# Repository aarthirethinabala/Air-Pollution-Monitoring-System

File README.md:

# Air Pollution Monitoring System
An Arduino-based air pollution and vehicle exhaust monitoring system designed to detect multiple gases and environmental conditions using gas sensors and a temperature/humidity sensor.

## Project Status
PCB Design Completed

## Overview
This project is designed to monitor air pollution using using multiple gas sensors connected to an Arduino Uno.
The system uses gas sensors to detect different pollutants and provides visual and audible indications based on the detected conditions.
Temperature and humidity are also monitored, and the readings can be displayed using an OLED display.
The PCB was designed as a controller and interface board, with the sensor modules connected externally through the provided connections.

## Components
- Arduino Uno
- MQ-7 gas sensor
- MQ-2 gas sensor
- MQ-135 gas sensor
- DHT22 temperature and humidity sensor
- OLED display
- Green LED
- Yellow LED
- Red LED
- Buzzer
- Resistors and supporting components

## Tools Used
- KiCad
- Schematic Editor
- PCB Editor
- 3D Viewer

## Design Process
The PCB was developed through the following stages:
1. Schematic design
2. Electrical Rules Check (ERC)
3. Footprint assignment
4. Component placement
5. Board outline creation
6. PCB routing
7. Copper zone creation
8. Design Rules Check (DRC)

## PCB Design
The completed PCB contains the Arduino interface connections, sensor connections, display connection, indicator LEDs, buzzer, and supporting circuitory.
The external sensor modules are connected to the PCB through their respective headers.

## Project Images
### Schematic

### PCB Layout

### 3D View

## What I Learned
- PCB schematic design
- ERC checking
- Footprint selection and assignment
- PCB component placement
- PCB routing
- Copper zones
- DRC checking
- Designing interfaces for external sensor modules

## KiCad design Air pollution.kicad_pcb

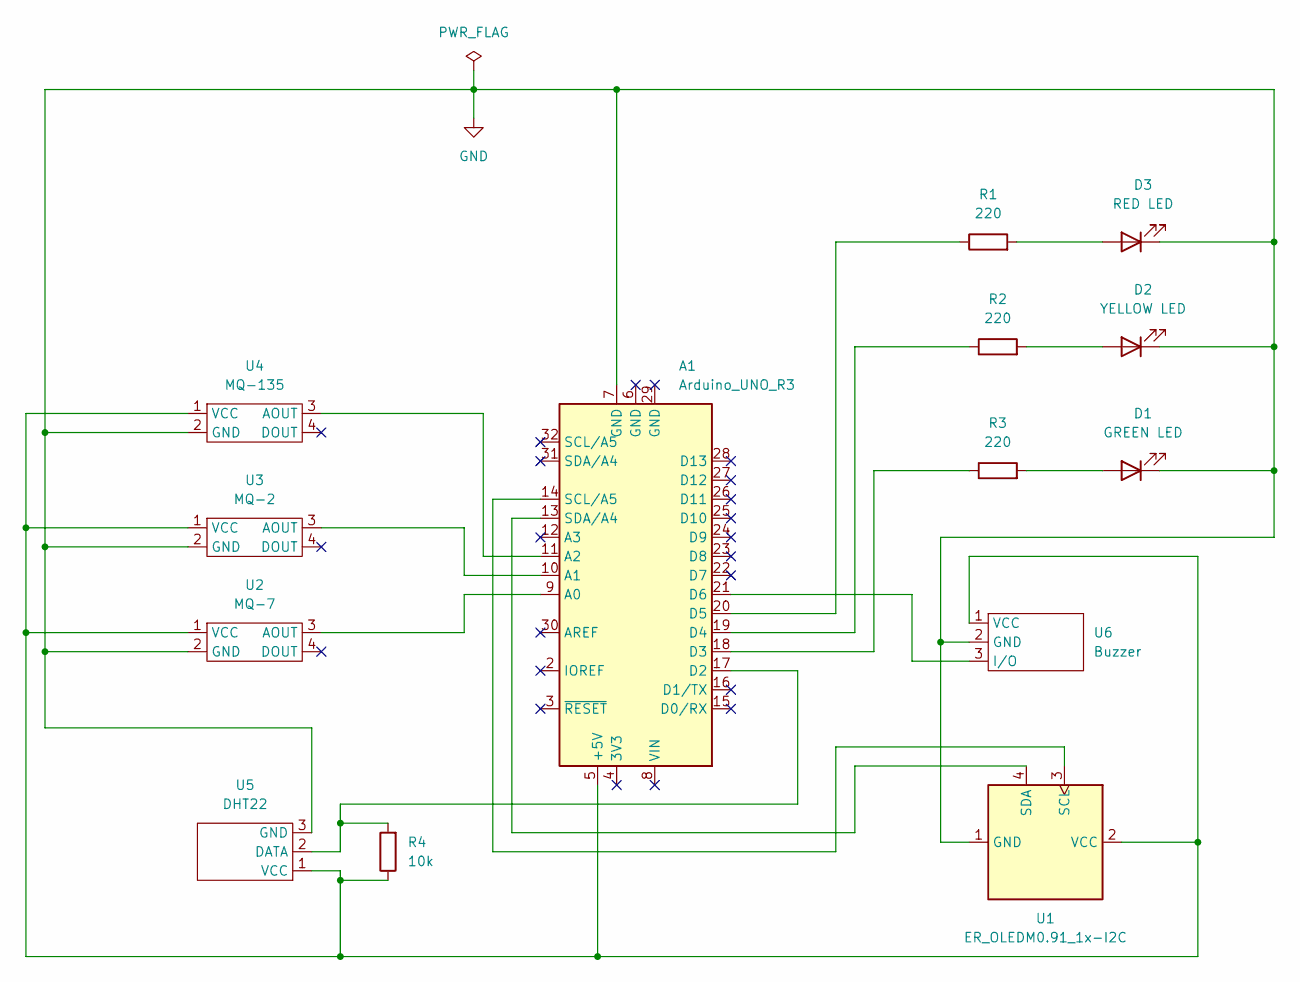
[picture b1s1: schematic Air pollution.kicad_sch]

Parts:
A1: Arduino_UNO_R3
D1: GREEN LED; LED_D5.0mm
D2: YELLOW LED; LED_D5.0mm
D3: RED LED; LED_D5.0mm
R1, R2, R3: 220; R_Axial_DIN0207_L6.3mm_D2.5mm_P7.62mm_Horizontal
R4: 10k; R_Axial_DIN0207_L6.3mm_D2.5mm_P7.62mm_Horizontal
U1: ER_OLEDM0.91_1x-I2C
U2: MQ-7
U3: MQ-2
U4: MQ-135
U5: DHT22
U6: Buzzer; Buzzer Module

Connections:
GND: A1.7 (GND), D1.1 (K), D2.1 (K), D3.1 (K), U1.1 (GND), U2.2 (GND), U3.2 (GND), U4.2 (GND), U5.3 (GND), U6.2 (GND)
unnamed: A1.5 (+5V), R4.1, U1.2 (VCC), U2.1 (VCC), U3.1 (VCC), U4.1 (VCC), U5.1 (VCC), U6.1 (VCC)
unnamed: A1.9 (A0), U2.3 (AOUT)
unnamed: A1.10 (A1), U3.3 (AOUT)
unnamed: A1.11 (A2), U4.3 (AOUT)
unnamed: A1.17 (D2), R4.2, U5.2 (DATA)
unnamed: A1.18 (D3), R3.1
unnamed: A1.19 (D4), R2.1
unnamed: A1.20 (D5), R1.1
unnamed: A1.21 (D6), U6.3 (I/O)
unnamed: D1.2 (A), R3.2
unnamed: D2.2 (A), R2.2
unnamed: D3.2 (A), R1.2
unnamed: A1.14 (SCL/A5), U1.3 (SCL)
unnamed: A1.13 (SDA/A4), U1.4 (SDA)

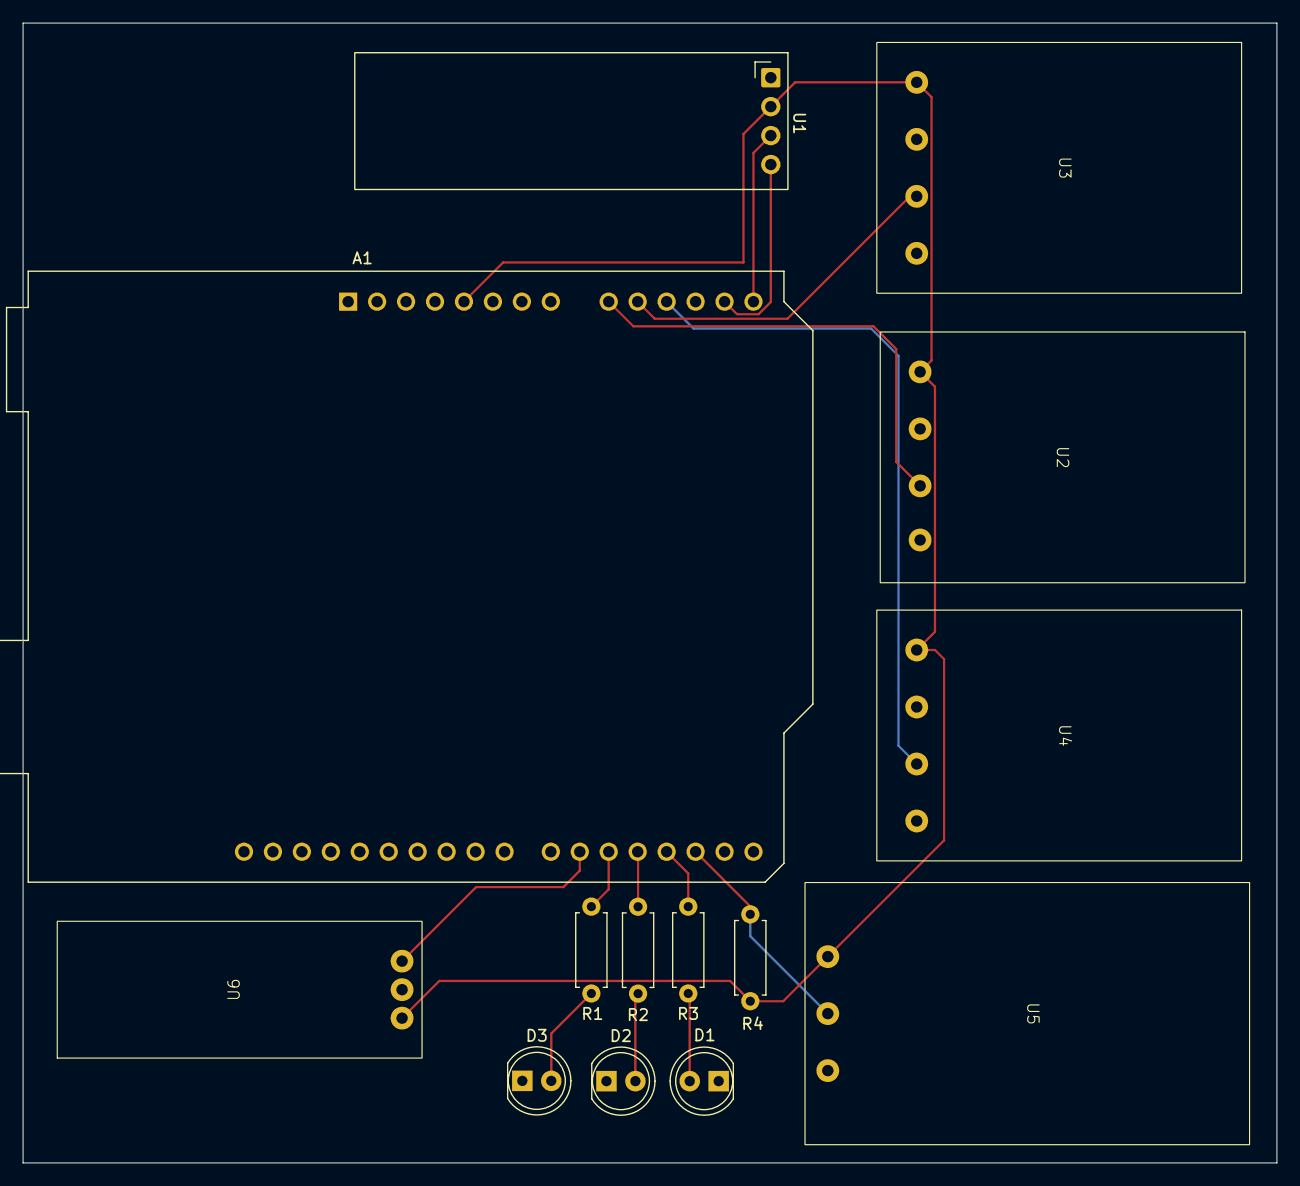
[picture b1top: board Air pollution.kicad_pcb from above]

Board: 2 copper layers, 110.0 x 100.0 mm, 14 parts (0 on the bottom side), 15 nets.
